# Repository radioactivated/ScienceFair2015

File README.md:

# ScienceFair2015

Files made in EAGLE for my science fair project

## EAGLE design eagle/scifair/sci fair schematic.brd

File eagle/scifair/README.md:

# ScienceFair2015
Files for my science fair project 2015
Schematic and board files made in EAGLE, with SparkFun libraries

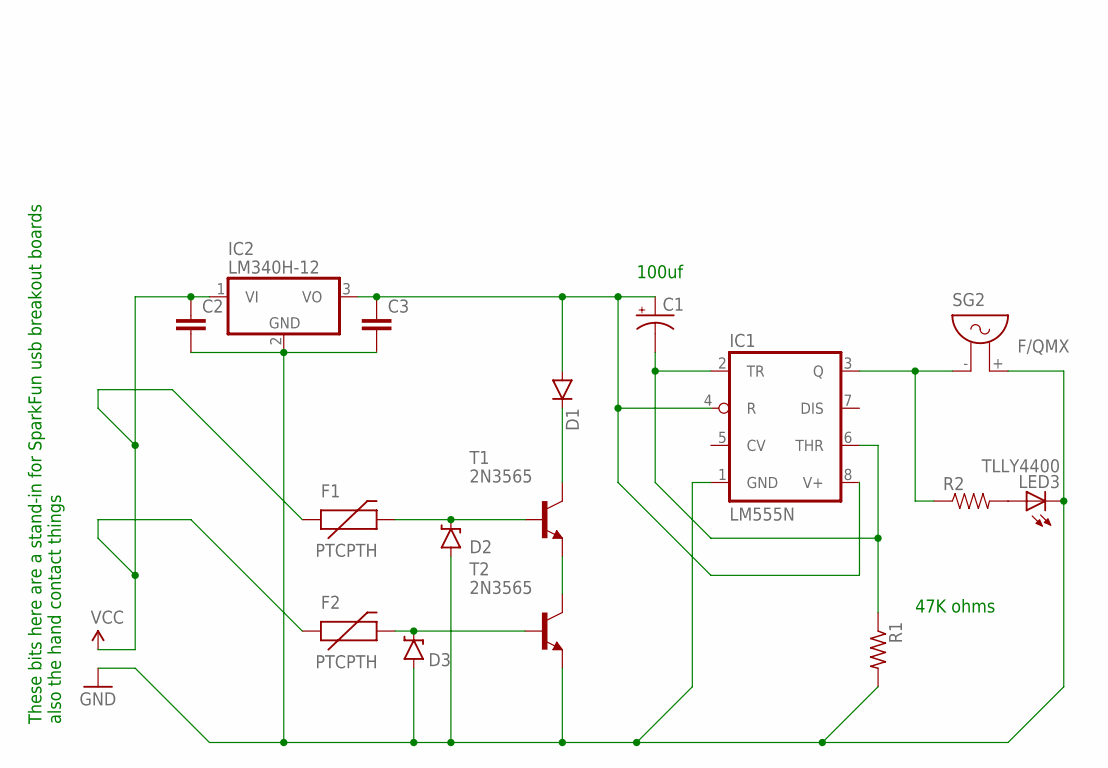
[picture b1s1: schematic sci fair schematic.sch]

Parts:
C1: CAP_POLPTH1; CPOL-RADIAL-100UF-25V
C2, C3: C5/2.5; C5B2.5
D1: DIODEPTH; DIODE-1N4001
D2, D3: DIODE-ZENERPTH; DIODE-ZENER
F1, F2: PTCPTH; PTC
IC1: LM555N; DIL08
IC2: LM340H-12; TO220H
LED3: TLLY4400; LED3MM
R1: R-US_0207/12; 0207/12
R2: RESISTORPTH-1/2W; AXIAL-0.5
SG2: F/QMX
T1, T2: 2N3565; TO92

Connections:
5V: C1.1 (+), C3.1, D1.A, IC1.4 (R), IC1.8 (V+), IC2.3 (VO)
GND: C2.2, C3.2, D2.P$2 (A), D3.P$2 (A), IC1.1 (GND), IC2.2 (GND), LED3.K (C), R1.2, SG2.+ (2), T2.3 (E)
unnamed: T1.3 (E), T2.1 (C)
unnamed: D1.C, T1.1 (C)
unnamed: D2.P$1 (C), F1.P$2 (2), T1.2 (B)
unnamed: D3.P$1 (C), F2.P$2 (2), T2.2 (B)
unnamed: IC1.3 (Q), R2.P$1 (1), SG2.- (1)
unnamed: C1.2 (-), IC1.2 (TR), IC1.6 (THR), R1.1
unnamed: LED3.A, R2.P$2 (2)
VCC: C2.1, F1.P$1 (1), F2.P$1 (1), IC2.1 (VI)

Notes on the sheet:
100uf
47K ohms
These bits here are a stand-in for SparkFun usb breakout boards also the hand contact things

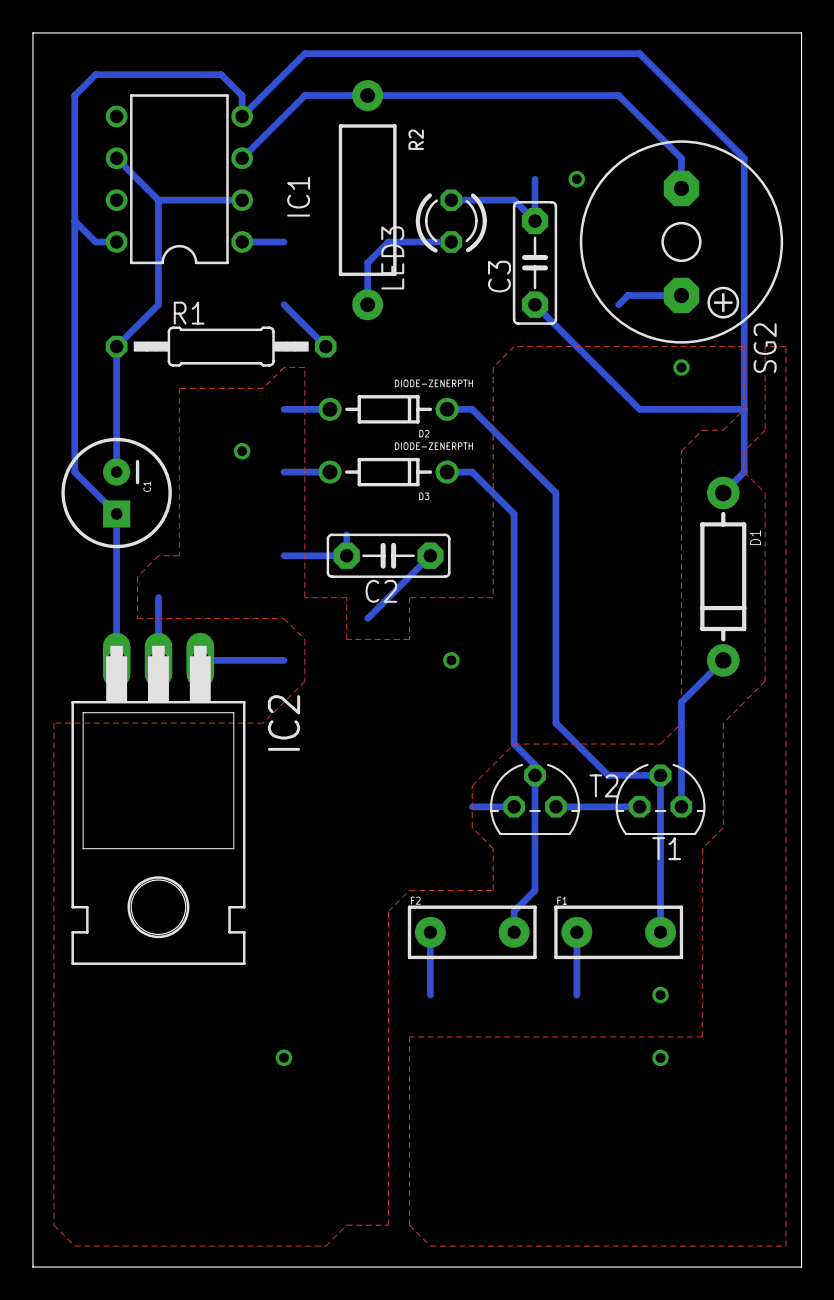
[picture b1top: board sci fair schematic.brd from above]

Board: 2 copper layers, 46.7 x 74.9 mm, 16 parts (0 on the bottom side), 10 nets.

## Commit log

2015-11-03 Document designs including new 555-chip one
2015-11-03 Add gitignore
2015-11-04 Clean up directories a bit
2015-11-04 Update changelog, 3 Nov 2015
2015-11-04 Add last-minute changes to research plan
2015-11-04 Rework design in entirety to solve issues with previous design
2015-11-04 Add directory for pcb designs which can be used in prototyping
2015-11-05 Add missing junctions for schematic clarity
2015-11-05 Some humorous warnings to keep nosy rubberneckers from messing stuff up
2015-11-05 Add a space using vias for jumpers to go to a rocker switch
2015-11-05 Move a wire over in sch for clarity
2015-11-05 Rework USB connections to use Sparkfun breakouts due to resource unavailability
2015-11-06 Rework board with copper pours and SparkFun USB breakout compatibility
2015-11-06 Update gitignore to ignore temporary lock files from LibreOffice
2015-11-06 Add extra copper pours for increased etching efficiency
2015-11-09 Start work on cost reduction, including eliminating SMD componenents (whose S&H were very high)
2015-11-09 Finalize cost-reduction design
2015-11-09 Fix potential via clearance problem in top-layer GND pour
2015-11-10 Tweak top-layer ground pour to be more efficient
2015-11-10 Remove extraneous vias in ground and VCC pours

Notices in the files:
parts and their libraries:
SparkFun-Capacitors: Licensing: Creative Commons ShareAlike 4.0 International - https://creativecommons.org/licenses/by-sa/4.0
